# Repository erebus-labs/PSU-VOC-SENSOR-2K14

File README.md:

PSU VOC SENSOR PROJECT
==============

The PSU VOC SENSOR PROJECT is a multi-board and software approach to sensor data collection, specifically targetting K20 classrooms - All on an open source HW/SW stack.

The mutli-board solution allows for the independant and decoupled developement of custom sensors, while the open software stack allows custom interpolation of sensor readings. 

- [ ] Note that Some USB Drivers/custom communication drivers still need to be reworked before the entire project can be released under some flavor of Open Source Licensing (e.g. GPL v3?)

All of the Hardware and Software developed is available, keeping in mind that future revisions and use must maintain open source licensing.

#Schematics

##Main Board

##Sensor Boards

#Code

##uC 

##GUI

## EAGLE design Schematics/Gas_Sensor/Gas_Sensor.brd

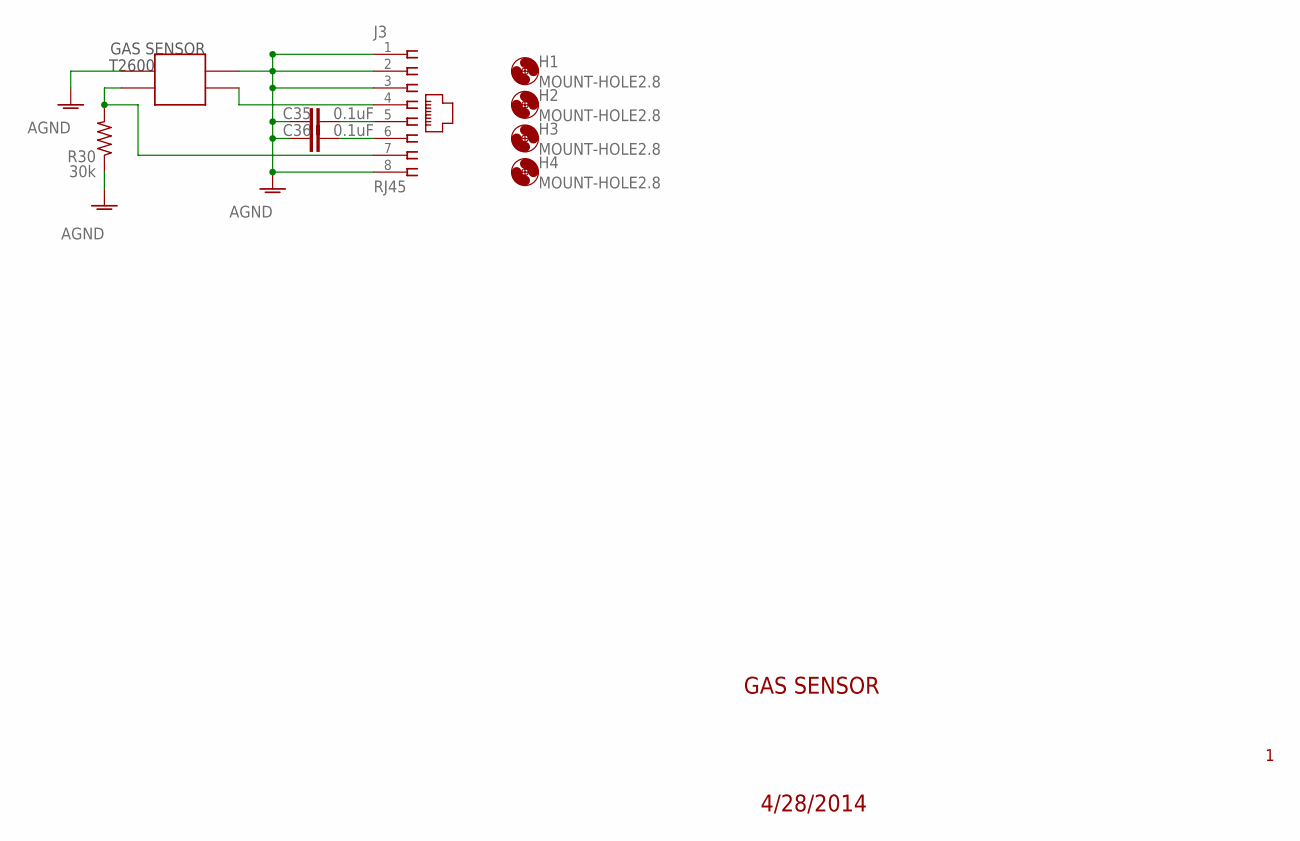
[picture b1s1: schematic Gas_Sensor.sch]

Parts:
C35, C36: 0.1uF; C0603K
H1, H2, H3, H4: MOUNT-HOLE2.8; 2,8
J3: RJ45; 555167-1
R30: 30k; R1206
X1: GAS_SENSOR

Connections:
AGND: C35.2, C36.2, J3.1, J3.2, J3.3, J3.8, R30.1, X1.P$1, X1.P$2
unnamed: J3.4, X1.P$3
unnamed: J3.7, R30.2, X1.P$4
unnamed: C36.1, J3.6
unnamed: C35.1, J3.5

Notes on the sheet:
GAS SENSOR
T2600
4/28/2014

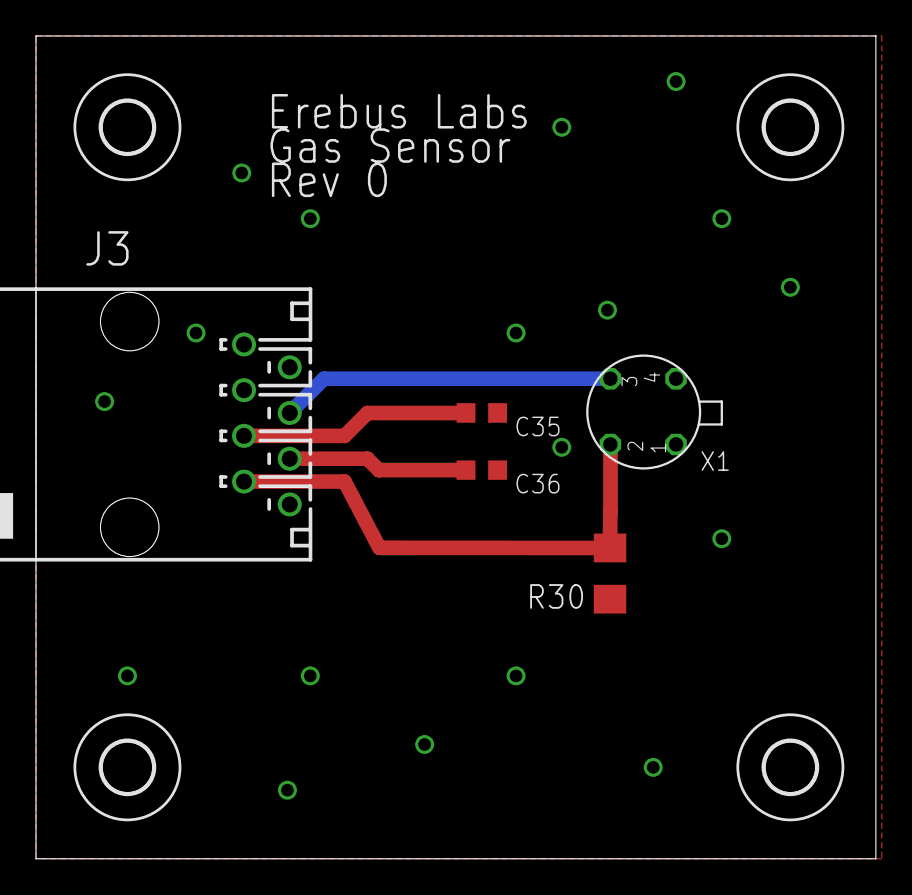
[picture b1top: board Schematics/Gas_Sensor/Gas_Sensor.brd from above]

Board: 2 copper layers, 46.7 x 45.7 mm, 9 parts (0 on the bottom side), 5 nets.

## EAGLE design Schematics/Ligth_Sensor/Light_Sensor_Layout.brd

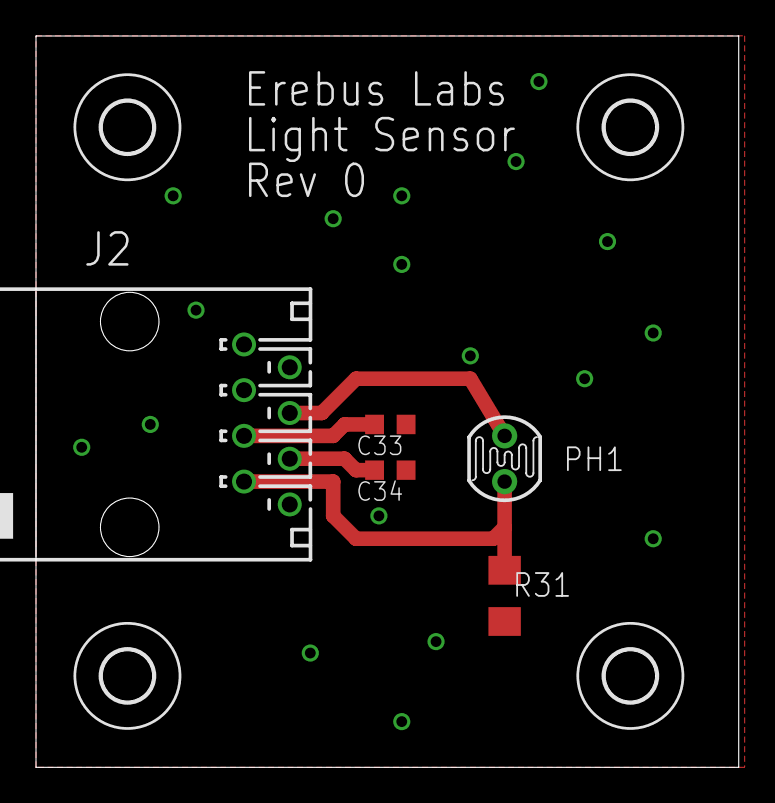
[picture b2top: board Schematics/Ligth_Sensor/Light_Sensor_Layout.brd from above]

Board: 2 copper layers, 39.0 x 40.6 mm, 9 parts (0 on the bottom side), 5 nets.

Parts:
C33, C34: 0.1uF; C0603K
H1, H2, H3, H4: MOUNT-HOLE2.8; 2,8
J2: RJ45; 555167-1
PH1: VT90N2; VT900
R31: 10k; R1206

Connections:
AGND: C33.1, C34.1, J2.1, J2.2, J2.3, J2.8, R31.1
unnamed: J2.4, PH1.1
unnamed: J2.7, PH1.2, R31.2
unnamed: C33.2, J2.5
unnamed: C34.2, J2.6

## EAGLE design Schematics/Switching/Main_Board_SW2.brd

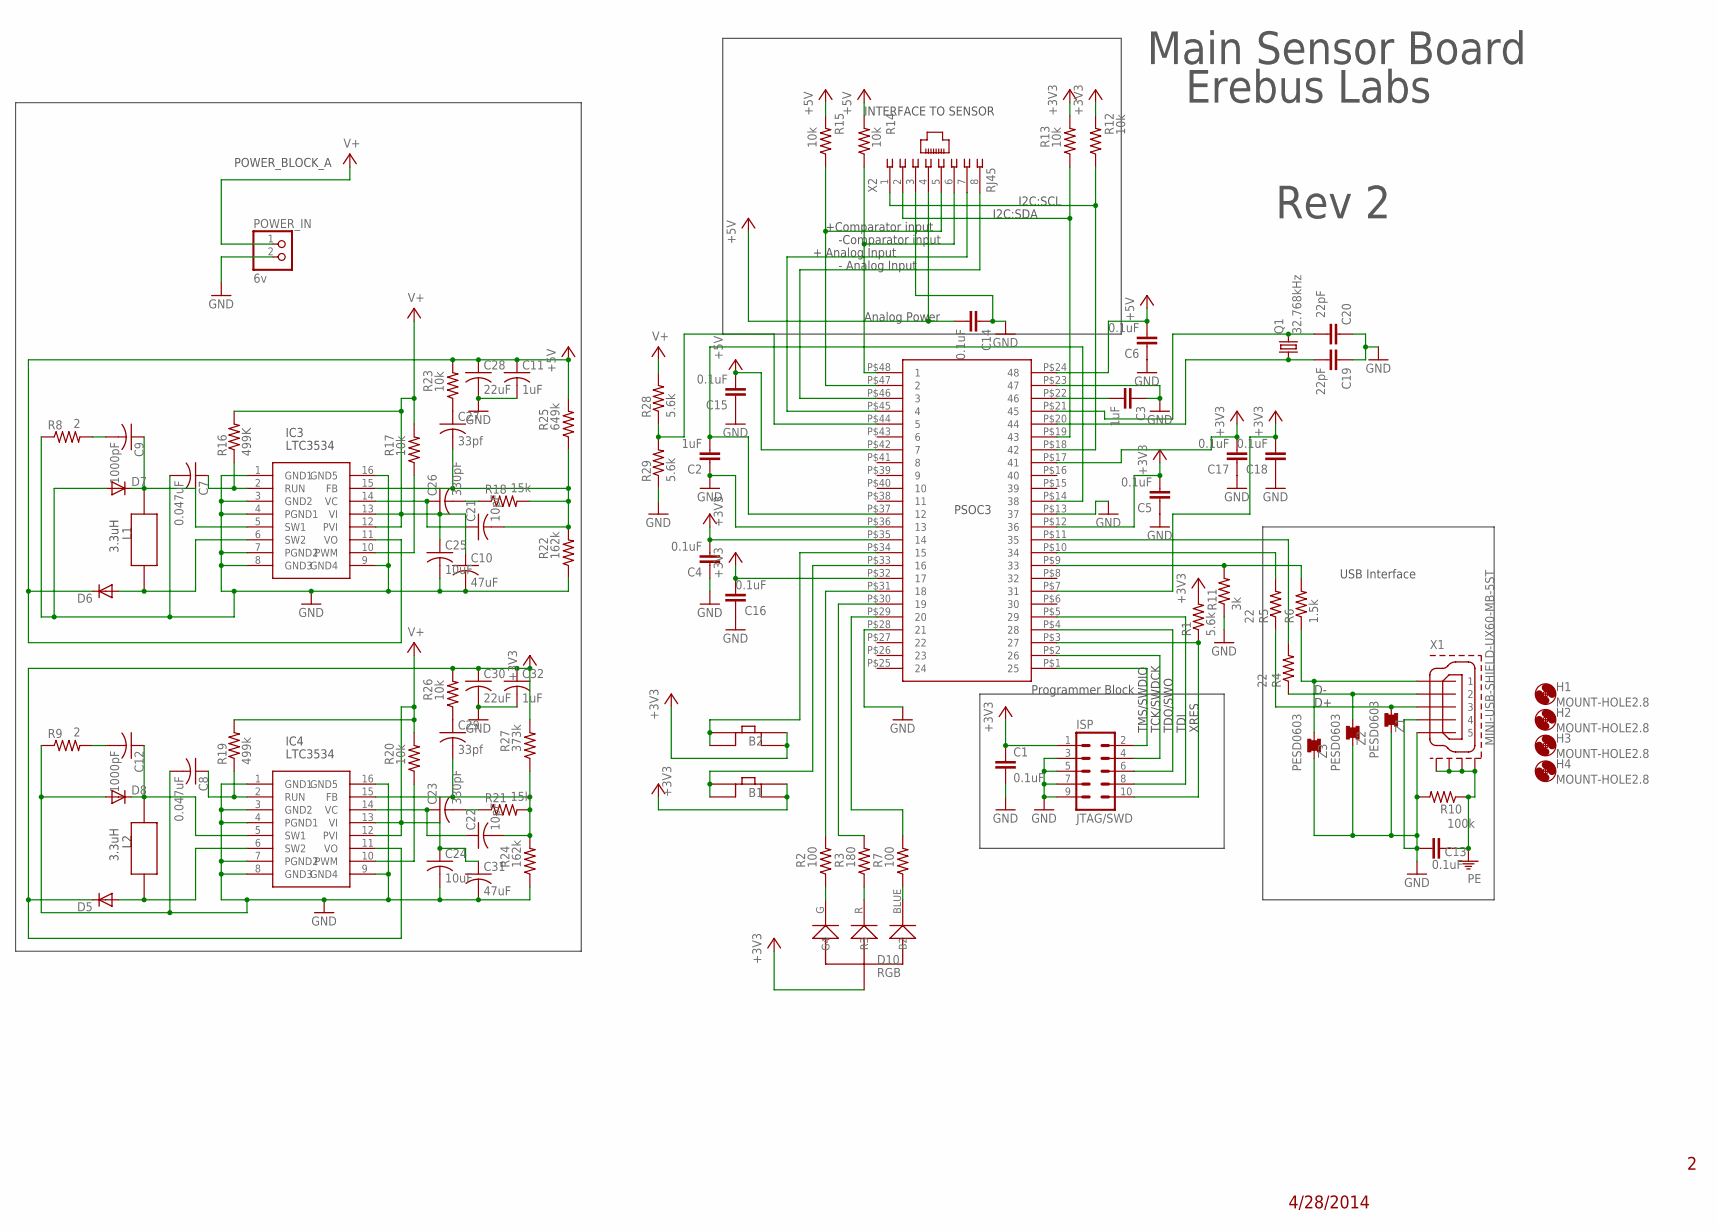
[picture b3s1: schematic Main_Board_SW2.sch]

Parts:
C1, C4, C5, C6, C13, C14, C15, C16, C17, C18: 0.1uF; C0603K
C2, C3, C11, C32: 1uF; C0603
C7, C8: 0.047uF; C0402
C9, C12: 1000pF; C0402
C10, C31: 47uF; C1210
C19, C20: 22pF; C0603
C21, C22: 10pF; C0805
C23, C26: 330pF; C0805
C24, C25: 10uF; C0805
C27, C29: 33pf; C0805
C28, C30: 22uF; C0805
D5, D6, D7, D8: DIODE-SOD323-R; SOD323-R
H1, H2, H3, H4: MOUNT-HOLE2.8; 2,8
IC3, IC4: SWITCHER; SSOP16
ISP: JTAG/SWD; FTSH-105-01-L-DV-K
L1: 3.3uH; SHEILDED_COIL
L2: 4.7uH; SHEILDED_COIL
POWER_IN: 6v; 1X02
Q1: 32.768kHz; TC38H
R1, R28, R29: 5.6k; R0805
R2, R7: 100; R0805
R3: 180; R0805
R4, R5: 22; R0603
R6: 1.5k; R0805
R8, R9: 2; R0402
R10: 100k; R0805
R11: 3k; R0805
R12, R13, R14, R15, R17, R20, R23, R26: 10k; R0805
R16: 499K; R0805
R18, R21: 15k; R0805
R19: 499k; R0805
R22, R24: 162k; R0805
R25: 649k; R0805
R27: 373k; R0805
RGB_LED: RGB_LED
U$1: PSOC_3_48PIN_SSOP
U$5, U$6: SPST
X1: MINI-USB-SHIELD-UX60-MB-5ST; UX60-MB-5ST
X2: RJ45; 555167-1
Z1, Z2, Z3: PESD0603; SMD-0603

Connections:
+3V3: C1.1, C4.2, C5.2, C16.2, C17.2, C18.2, C30.1, C32.1, D5.C, IC4.11 (VO), ISP.1, R1.2, R12.2, R13.2, R26.2, R27.2, RGB_LED.VCC (VCC1), U$1.P$7 (31), U$1.P$12 (36), U$1.P$17 (41), U$1.P$32 (17), U$1.P$35 (14), U$5.B1, U$5.B2, U$6.B1, U$6.B2
+5V: C6.2, C11.1, C14.2, C15.2, C28.1, D6.C, IC3.11 (VO), R14.2, R15.2, R23.2, R25.2, U$1.P$24 (48), U$1.P$42 (7), X2.4
ANALOGINPUT: U$1.P$46 (3), X2.8
GND: C1.2, C2.1, C3.1, C4.1, C5.1, C6.1, C7.2, C8.2, C10.2, C11.2, C13.2, C14.1, C15.1, C16.1, C17.1, C18.1, C19.1, C20.1, C24.2, C25.2, C28.2, C30.2, C31.2, C32.2, D7.A, D8.A, IC3.1 (GND1), IC3.3 (GND2), IC3.4 (PGND1), IC3.7 (PGND2), IC3.8 (GND3), IC3.9 (GND4), IC3.16 (GND5), IC4.1 (GND1), IC4.3 (GND2), IC4.4 (PGND1), IC4.7 (PGND2), IC4.8 (GND3), IC4.9 (GND4), IC4.16 (GND5), ISP.3, ISP.5, ISP.7, ISP.9, POWER_IN.2, R8.1, R9.1, R10.2, R11.1, R22.1, R24.1, R29.1, U$1.P$13 (37), U$1.P$23 (47), U$1.P$28 (21), U$1.P$36 (13), X1.4, X1.5, X2.3, Z1.1, Z2.1, Z3.1
unnamed: R4.2, U$1.P$11 (35)
unnamed: R5.2, U$1.P$10 (34)
unnamed: R6.2, R11.2, U$1.P$9 (33)
unnamed: ISP.2, U$1.P$1 (25)
unnamed: ISP.4, U$1.P$2 (26)
unnamed: ISP.6, U$1.P$4 (28)
unnamed: ISP.8, U$1.P$5 (29)
unnamed: ISP.10, R1.1, U$1.P$3 (27)
unnamed: C2.2, U$1.P$14 (38), U$1.P$37 (12)
unnamed: R2.1, RGB_LED.G (G4)
unnamed: C3.2, U$1.P$22 (46)
unnamed: R3.1, RGB_LED.R (R3)
unnamed: R5.1, X1.3, Z1.2
unnamed: R4.1, X1.2, Z2.2
unnamed: R7.1, RGB_LED.BLUE (B2)
unnamed: C20.2, Q1.2, U$1.P$21 (45)
unnamed: R6.1, X1.1, Z3.2
unnamed: R15.1, U$1.P$47 (2), X2.5
unnamed: R14.1, U$1.P$48 (1), X2.6
unnamed: R12.1, U$1.P$18 (42), X2.1
unnamed: R28.1, R29.2, U$1.P$44 (5)
unnamed: C19.2, Q1.1, U$1.P$20 (44)
unnamed: C21.1, C26.1, IC3.14 (VC)
unnamed: C7.1, IC3.2 (RUN), R16.1
unnamed: C9.1, D7.C, IC3.5 (SW1), L1.P$2
unnamed: IC3.10 (PWM), R17.1
unnamed: D6.A, IC3.6 (SW2), L1.P$1
unnamed: C26.2, R18.1
unnamed: C21.2, C27.2, IC3.15 (FB), R18.2, R22.2, R25.1
unnamed: C27.1, R23.1
unnamed: C8.1, IC4.2 (RUN), R19.1
unnamed: IC4.10 (PWM), R20.1
unnamed: C12.1, D8.C, IC4.5 (SW1), L2.P$2
unnamed: D5.A, IC4.6 (SW2), L2.P$1
unnamed: C22.1, C23.1, IC4.14 (VC)
unnamed: C23.2, R21.1
unnamed: C22.2, C29.2, IC4.15 (FB), R21.2, R24.2, R27.1
unnamed: C29.1, R26.1
unnamed: U$1.P$34 (15), U$5.A1, U$5.A2
unnamed: U$1.P$45 (4), X2.7
unnamed: R2.2, U$1.P$31 (18)
unnamed: U$1.P$33 (16), U$6.A1, U$6.A2
unnamed: R3.2, U$1.P$30 (19)
unnamed: R7.2, U$1.P$29 (20)
unnamed: R13.1, U$1.P$19 (43), X2.2
unnamed: C9.2, R8.2
unnamed: C12.2, R9.2
PE: C13.1, R10.1, X1.M1 (GND1), X1.M2 (GND2), X1.M3 (GND3), X1.M4 (GND4)
V+: C10.1, C24.1, C25.1, C31.1, IC3.12 (PVI), IC3.13 (VI), IC4.12 (PVI), IC4.13 (VI), POWER_IN.1, R16.2, R17.2, R19.2, R20.2, R28.2

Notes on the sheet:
PSOC3
TMS/SWDIO
TCK/SWDCK
TDO/SWO
TDI
XRES
Programmer Block
INTERFACE TO SENSOR
USB Interface
+Comparator input
-Comparator input
- Analog Input
I2C:SCL
I2C:SDA
3.3uH
POWER_BLOCK_A
Erebus Labs
Main Sensor Board
Rev 2
IC3
IC4
LTC3534
Analog Power
+ Analog Input
4/28/2014
D10
RGB

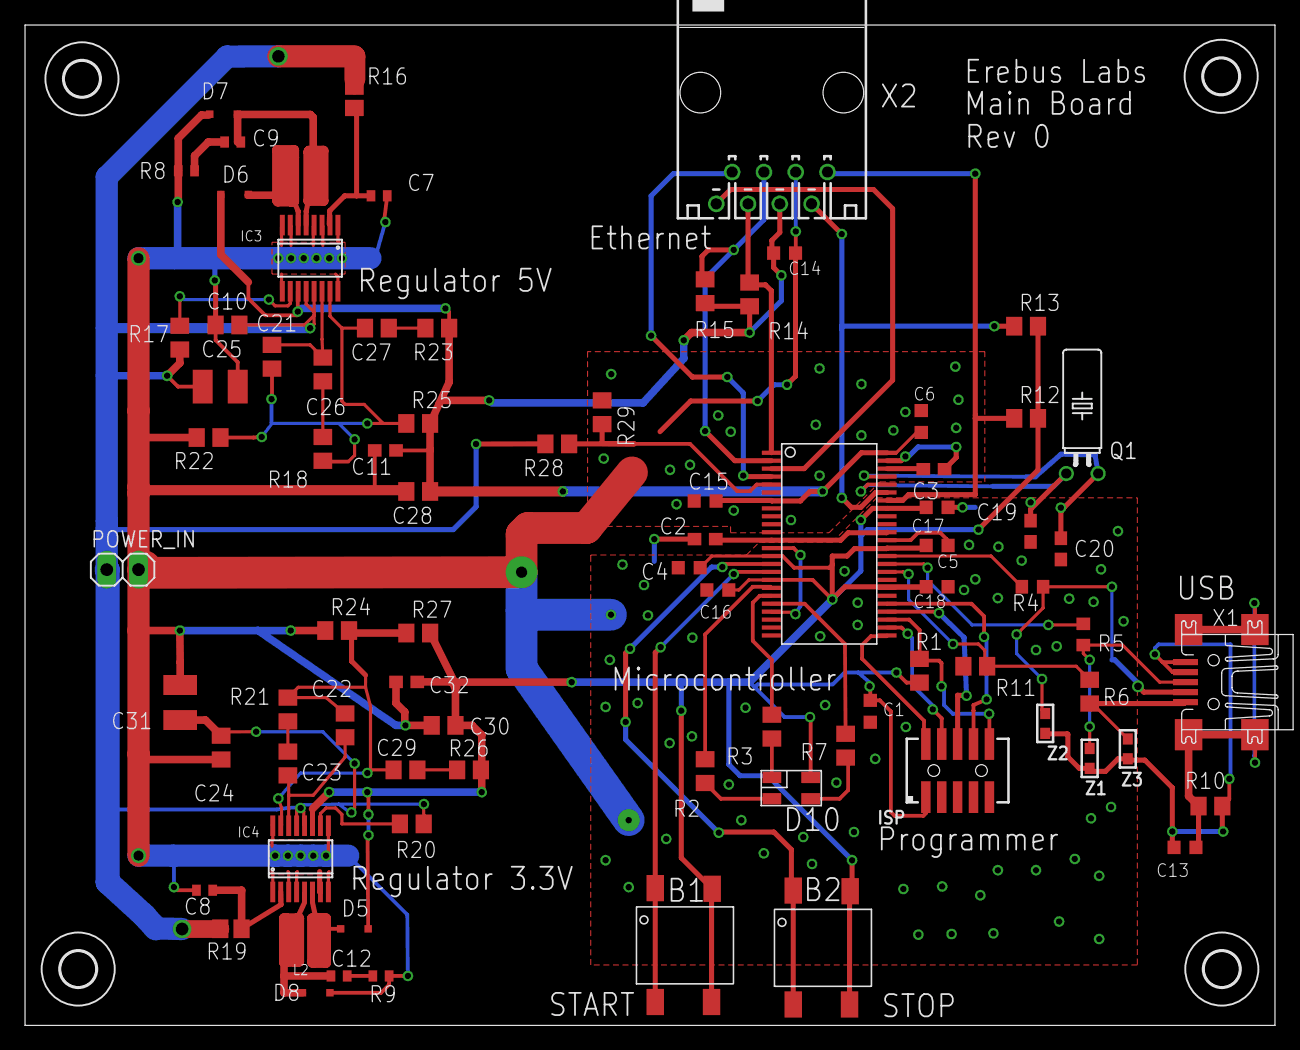
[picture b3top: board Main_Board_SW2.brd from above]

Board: 2 copper layers, 99.9 x 80.0 mm, 85 parts (0 on the bottom side), 53 nets.

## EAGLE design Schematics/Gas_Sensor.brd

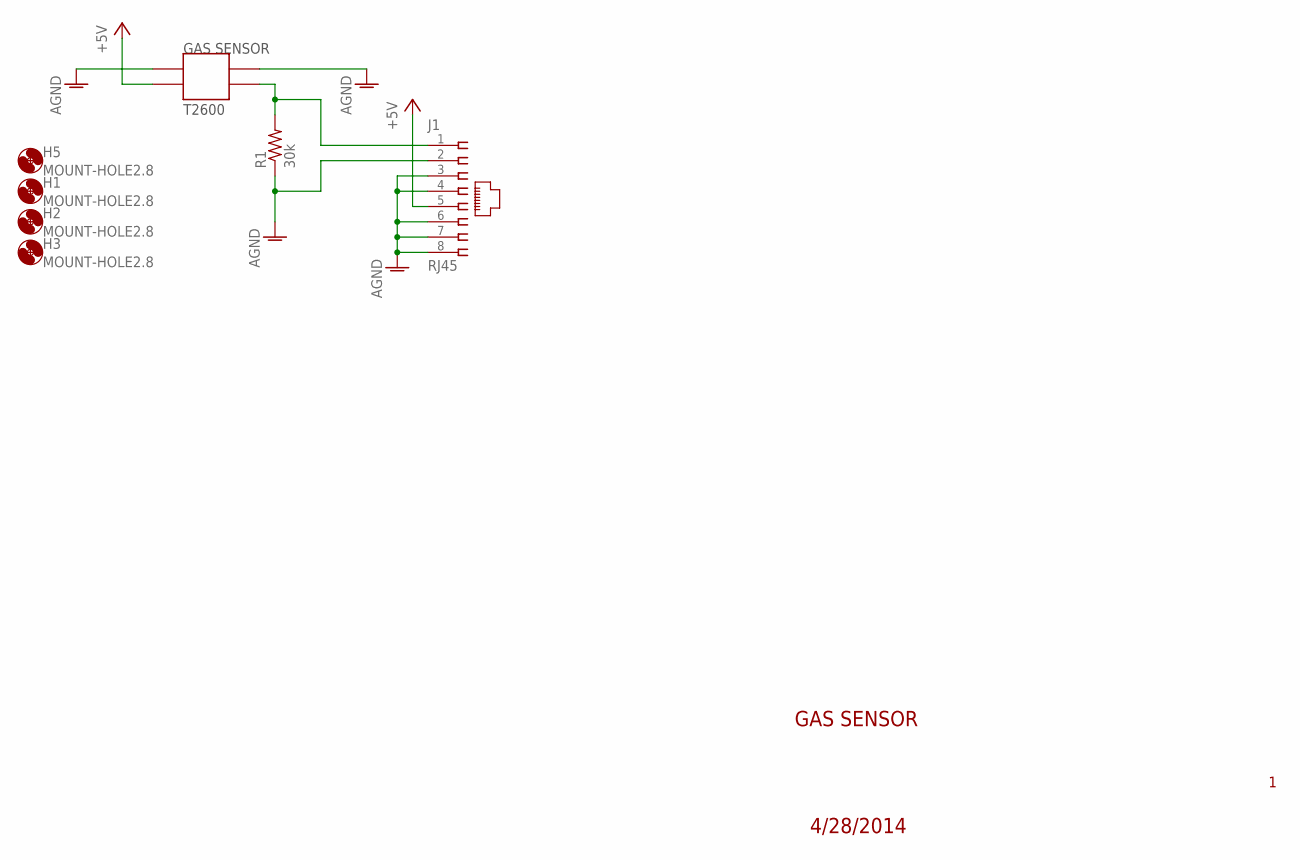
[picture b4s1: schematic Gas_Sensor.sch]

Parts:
H1, H2, H3, H5: MOUNT-HOLE2.8; 2,8
J1: RJ45; 555167-1
R1: 30k; R1206
U$1: GAS_SENSOR

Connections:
+5V: J1.5, U$1.P$3
AGND: J1.2, J1.3, J1.4, J1.6, J1.7, J1.8, R1.1, U$1.P$1, U$1.P$2
unnamed: J1.1, R1.2, U$1.P$4

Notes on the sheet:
GAS SENSOR
T2600
4/28/2014

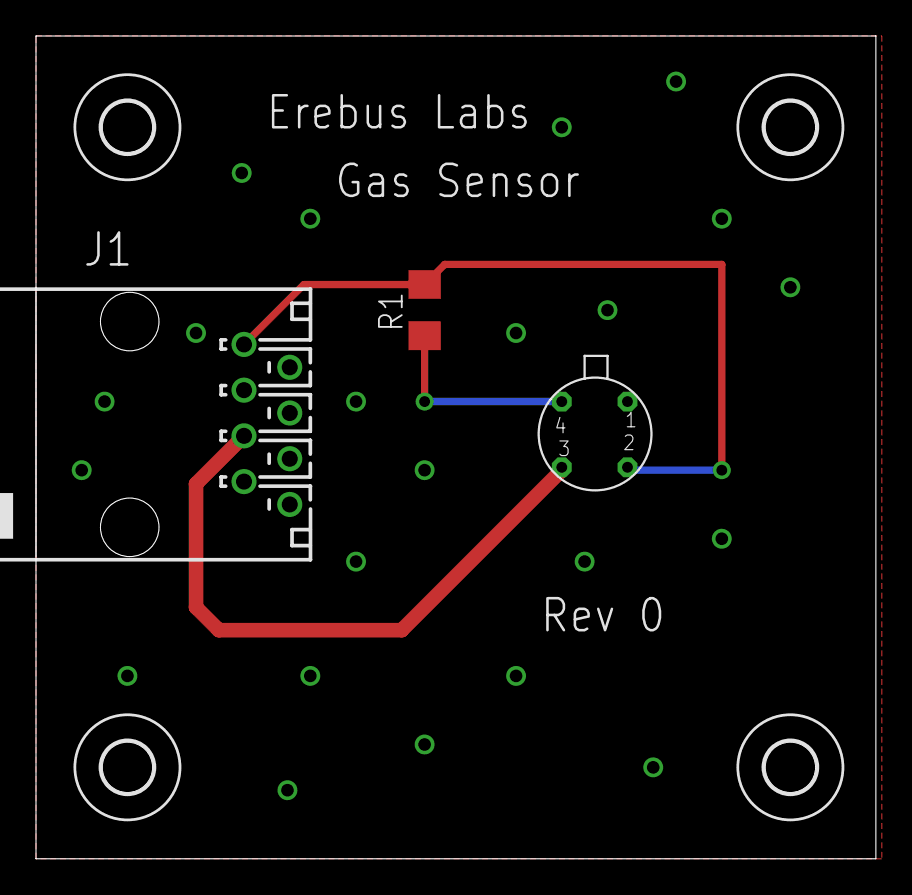
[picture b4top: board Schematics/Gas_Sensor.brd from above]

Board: 2 copper layers, 46.7 x 45.7 mm, 7 parts (0 on the bottom side), 3 nets.

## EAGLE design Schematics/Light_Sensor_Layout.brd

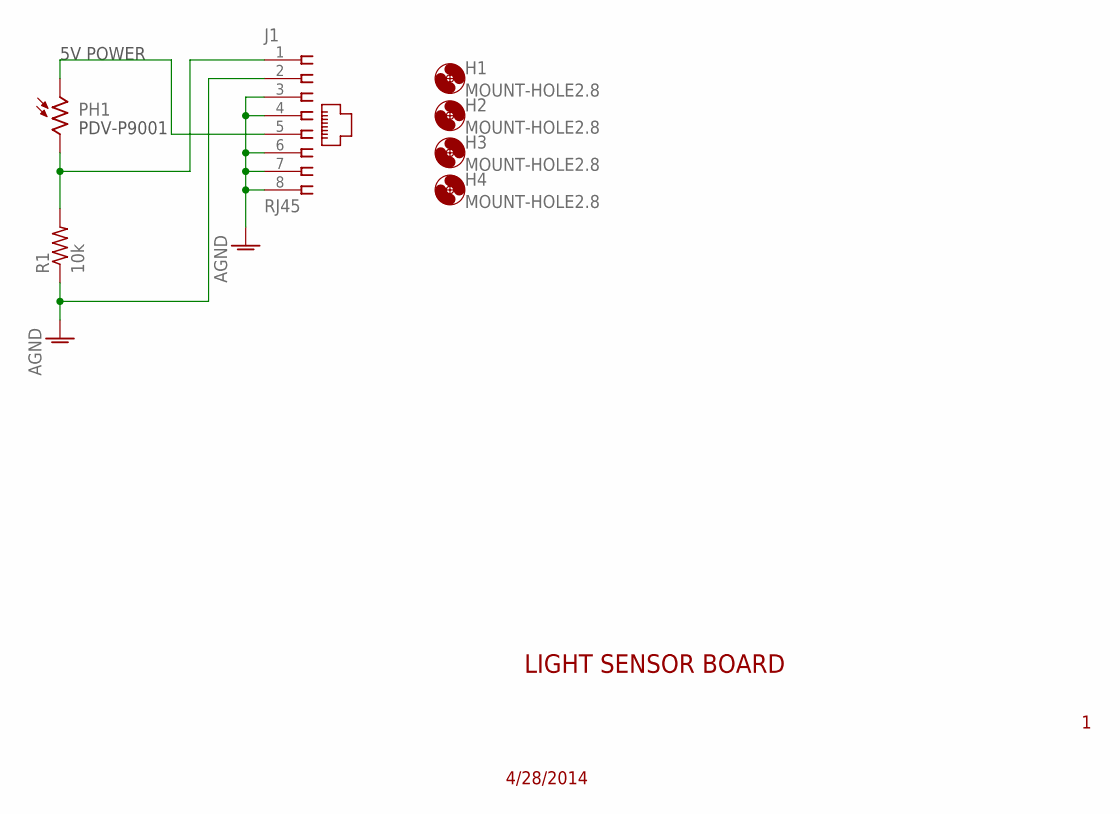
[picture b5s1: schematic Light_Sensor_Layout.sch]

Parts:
H1, H2, H3, H4: MOUNT-HOLE2.8; 2,8
J1: RJ45; 555167-1
PH1: VT83N2; VT800
R1: 10k; R1206

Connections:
AGND: J1.2, J1.3, J1.4, J1.6, J1.7, J1.8, R1.1
unnamed: J1.5, PH1.1
unnamed: J1.1, PH1.2, R1.2

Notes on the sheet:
PDV-P9001
5V POWER
LIGHT SENSOR BOARD
4/28/2014

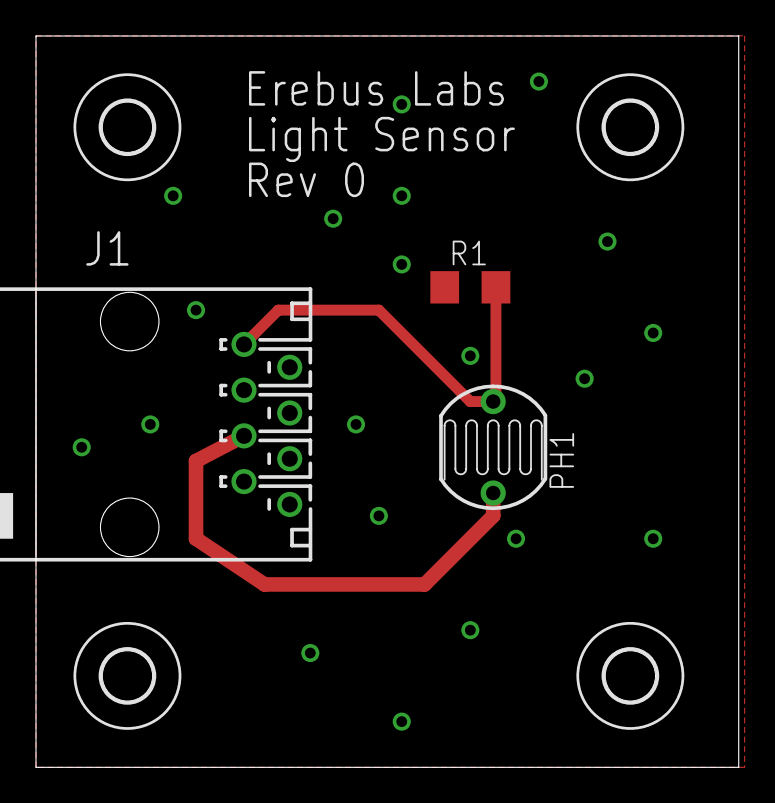
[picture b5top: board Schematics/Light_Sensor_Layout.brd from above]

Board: 2 copper layers, 39.0 x 40.6 mm, 7 parts (0 on the bottom side), 3 nets.

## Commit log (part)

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2013-12-27 Push test
2013-12-28 Test to see if I can update.
2013-12-28 Possible Parts
    Some parts that might work. The micrcontoller is probably to expensive.
2013-12-31 Added V1.0 of requirements doc
2013-12-31 Created /Documents folder, added initial requirements doc
2014-01-03 Needs Statments
    There are some format errors that show up whan saving an open offfice
    file as a .doc file
2014-01-03 Delete .~lock.Erebus_Needs.doc#
    Not sure why this file was created
2014-01-04 Initial Build
2014-01-04 Added objective and background document.
2014-01-04 Updated Requirements doc
2014-01-07 Removed Documents/Erebus_Needs.docx
2014-01-07 Delete .~lock.test 1.txt#
    Not sure why I made this, so it was removed
2014-01-08 Revert "Delete .~lock.test 1.txt#"
    This reverts commit 3fadf2508f8f2172cbb31cd926eae070e93d5b1f.
2014-01-08 Test 2
2014-01-08 Added references
2014-01-12 Added Documents/Budget.docx
2014-01-12 Removed testfile.c
2014-01-13 Initial Build. Needs Content
    Just an initial build. I need to fix some formatting and add some
    content, but I just wanted to put this up to show everyone the general
    theme so we have time to change things before the meeting.
2014-01-13 Fixed Name.
2014-01-13 Formatted Tables
2014-01-13 Added Content. Diagrams and Milestones
2014-01-13 Original File for System Diagram.
2014-01-13 Original File for Interfacing Diagram.
2014-01-14 Renamed. Should not be labeled as a build.
2014-01-14 Updated Proposal
2014-01-15 Create gh-pages branch via GitHub
2014-01-18 Temp sensor
2014-01-19 Removed old proposal PDF
2014-01-19 Updated proposal to v1.3
2014-01-19 Removed Erebus_Needs.doc from main directory
2014-01-19 Removed PSoC 4100 Family datasheet
2014-01-20 Added microcontroller specifications for top 3 candidates
2014-01-22 Updated uController specs
2014-01-22 Quick Meeting Notes
2014-01-23 Updated Microcontroller_Specs.xlsx with PCB costs
2014-01-23 Added initial software plan
2014-01-24 Added preliminary block diagram file. File contains multiple pages with different levels.
    Requires MS Visio
2014-01-25 Updated with lower level diagrams (1 and 2) as well as block diagram from datasheet for ucontroller.
2014-01-25 No longer needed
2014-01-27 Cleaned up microcontroller datasheets
2014-01-30 Timeline. Added Hardware/Firmware Subtasks. ~80% Complete
2014-01-31 Replaced TI datasheets with Cypress datasheets for PSoC3
2014-01-31 Removed obsolete documents
2014-01-31 Possible emperature sensor
2014-01-31 Temperature sensor
    Cheaper version of previous one.
2014-01-31 Not using
2014-01-31 Updated Budget to v1.3
2014-02-01 Updated Design Spec and Budget
2014-02-02 Added contacts document
2014-02-02 Added contact list document
2014-02-16 Added Highlights to ADC Section
2014-02-16 Added Cypress ADC Example
2014-02-16 Added ADC Datasheet with Highlights
2014-02-16 Added Figaro Sensor Datasheets with Highlights.
2014-02-23 Early version of main board schematic
2014-03-01 Added Highlights to Emulated EEPROM
2014-03-04 Updated Design Specification with USB details
2014-03-14 Initial Push of Max Code Folder
2014-03-14 Added dev board user guide
2014-03-15 Added EEPROM datasheet
2014-03-21 Mac Code Update
2014-03-24 Updated Scott Project files, added datasheets, initial push of Python Script
2014-03-27 Added USB communication protocol and EEPROM access functions
2014-03-27 Repush Repush
2014-03-27 Created Demo Build. Merged Code
2014-03-27 Updated communication script
2014-03-27 Updated Demo Code
2014-03-28 Push Code
2014-03-28 Added Interrupt Documentation
2014-03-28 Completed USB data dump method
2014-03-28 Fixed Data dump methods
2014-03-29 Updated Schematic
    Grounds and voltages are not set yet. Most are place holders for the
    moment.
2014-03-30 Updated Design Spec to v1.4
2014-03-30 Fixed typos in Design Spec
2014-04-01 Updated Design Spec to v1.5
2014-04-01 Added files for Bryan
    Added code to folder for testing power management and RTC interrupt
    controls.
2014-04-02 Initial push of gui.py
2014-04-02 Implemented EEPROM variable pointers
2014-04-02 Changed incoming stream parsing to count bytes instead of data samples
2014-04-02 Spread Sheet did not port to pdf properly
2014-04-09 Update push
2014-04-10 Added hard_reset() and EEPROM variables, removed blinking LED
2014-04-10 Updated master to match Scott code from commit 5fe109704ac546addd07589f49c463d76ea794e6
2014-04-10 Cleaned up python directory, created simple interface
2014-04-10 Updated PM code, added reference doc
    Added RTC interrupt mask functions
    Added RTC sample unit check
    Added Sample code
    Added C reference document
2014-04-13 Updated GUI Layout: Added buttons, frames, and menu
2014-04-14 Restructured GUI file layout. Began integrating sensor class with GUI - sensor now connects.
2014-04-15 Add switcher circuit
2014-04-15 BOM and schematic update
    Still missing push button interface and sensor breakouts
2014-04-20 File Cleaning
2014-04-23 Misc changes to power mgmt code
2014-04-25 Stuff
2014-04-26 Massive changes to master. Rearranged layout, added multiple sample block data support, added button interrupts, added send configuration routine, added data sample block headers
2014-04-26 Small fix on pin1 of psoc
2014-04-26 Changed command format to single byte
2014-04-28 Fixed applying and retrieving settings changes
2014-04-28 Created BreadBoardBuild in Master folder. Began Pin assign
    USB is Set. VDDD VDDA VDDIO Set. Questions on JTAG
2014-04-28 Fixed multiple sample block transfer and button interrupts
2014-04-28 Fixed multiple sample block transfers
2014-04-29 Mostly updates with some sensor stuff
2014-04-30 Fixed timestamps on data samples
2014-04-30 Added recognition of empty data sets
2014-05-01 Updates for pin assignments
2014-05-02 Fixed sample function not being called Changed sleep function call values to match Cypress defined variables Changed sleep time to "none"
    Sample counter not correctly detecting when sample should occur based on given interval
2014-05-02 Removed LED test code from everywhere but the sample function
2014-05-02 Button Updates
2014-05-02 Sleep functionality working Sample functionality working
    Removed unneeded interval unit masks
    standardized function names
2014-05-02 Deleted Initial BreadBoardBuild.
2014-05-02 Fixed interface.py handling of multi-packet data transfers, cleaned up unnecessary files
2014-05-02 Fixed multi-packet data dumps with extra interlocking and zero-length packets
2014-05-06 Cleaned up some power code
    Added initial poster template with base design
2014-05-07 Broken code checkpoint. LED controls added, debouncers removed, sleep code ifdef'd off
2014-05-08 Switching Layout Placed
2014-05-08 Fixed sample start/stop with sleep. Added RGB LED Control. Reorganized code tree and added macro and global header files.
2014-05-08 Layout Update
2014-05-08 Began PCB Verify. Slight Modifications to Gas Sensor Module during verify.
2014-05-09 LDO Layout
2014-05-10 Added Drill Holes. Moved Traces. Moved Silkscreen References
2014-05-11 Added low power LED blinking. Added more 3rd party docs.
2014-05-11 Layout for final inspection
2014-05-12 Added Poster
2014-05-12 Added grading rubric files
2014-05-12 Manufacturer part number updates
2014-05-12 PCB Verify Push. Status: In Progress
2014-05-12 Updated Switcher Board
2014-05-13 PCB Verified. Add Battery Sense
2014-05-13 Batter Sense
2014-05-13 Hopeful pull
2014-05-13 Updated Board PNGs
2014-05-13 Last layout sync of night
2014-05-15 Dimensions for each of the boards
2014-05-17 Added board enclosure files
2014-05-19 Flash persistence/wear-levelling implemented - corner cases not yet tested
2014-05-19 Implemented reset code in GUI. Removed save/restore settings options.
2014-05-19 Updated logo
    Updated Poster.pptx
    + Added Overview
    + Added references
    =Updated schematic printouts
    =Updated team info
    Added board enclosures (box) files
2014-05-20 Restored zero-length packet on sample export. Data persistence implementation complete. Pointer wrapping and memory full condition untested.
2014-05-20 Merged host/device replies, switch order of command characters. Moved next command in data dump.
2014-05-20 Added sucess messages to reset and data export
2014-05-24 Added comments to all functions
2014-05-24 Added docstrings and additional comments to GUI scripts
2014-05-26 Updated Poster.pptx +Added additional graphics =Changed som formatting and layout of overview =Changed layout of team section
2014-05-26 Cleaned up stuff
    Made Schematics easier to read
    Split Supplies in BOM and made names match references
    Renamed parts on sensor
2014-05-26 Changed Poster.pptx +Added final result section =Formatting adjustments =Moved objective to yellow section -Removed second overview paragraph -Less words
2014-05-27 Updated Poster.pptx to preliminary final version *Missing GUI pic *Missing Team pics *Needs proof reading and confirmation from team-mates
    Added PDF version of poster
2014-05-27 Fixed indentation errors in GUI script
2014-05-27 Small grammatical changes
2014-05-27 Thank god for version control
    Wrote over the wrong one
2014-05-27 Added Notes .pdf for Poster
2014-05-27 Added poster back or whatever
2014-05-28 Final version of Poster.pptx including initial feedback
2014-05-28 Poster stuff
2014-05-28 Minor adjustments to final poster
2014-05-29 Pushed up old file that got over worte
2014-05-30 Created Dev Board Master and Master. Updated IO for PCB
2014-05-31 Added notification box on settings application completion
2014-05-31 Fixed misnamed reset function call
2014-05-31 Is this the code youre looking for?
2014-06-02 Removed Scott's code folder
2014-06-02 Removed Max's code folder
2014-06-02 Removed DemoBuild code folder
2014-06-02 Removed extraneous text file from code folder
2014-06-02 Renamed master to master_pcb
2014-06-02 Updated master_pcb with correct pin assignments
2014-06-02 Removed incomplete file submission (Master folder)
2014-06-02 Removed every second battery check used for debugging
2014-06-02 Refactored button masks and PICU register out of RTC interrupt file
2014-06-02 Updated master_devboard with fixes from master_pcb
2014-06-02 Updated Project timeline. Original project file corrupted and removed, pdfs provided
2014-06-02 Removed old timeline pdf
2014-06-02 Updated budget with PCB and Digikey order info
2014-06-02 Added Cypress USBUART Windows drivers
2014-06-03 Cost for single unit
2014-06-03 Added sensor and power section to design specs.
2014-06-03 Added to the budget
2014-06-04 Added presentation file
2014-06-04 User Manual
2014-06-05 Initial Push of Basic STEM Lesson
    In Scott's favorite format. (Sorry)
2014-06-05 v1.6 of Design Spec
2014-06-05 Reorganized Documents Directory
2014-06-05 Fixed layout of BOM
2014-06-05 Added Technical Reference Manual
2014-06-05 Added Technical Reference Manual source doc, removed extra TRM PDF
2014-06-05 Fundamentals Edit. Moved some 3rd_Party_Docs
2014-06-05 Updated presentation to Final Rough Draft
2014-06-05 Changed sensor #1 to Gas sensor, added sensor #2: Custom sensor
2014-06-05 Added support for opening reference documents
2014-06-05 Added reference documents for GUI use
2014-06-06 Pushed The Test Plan! Update Format.
2014-06-06 Updated presentation
2014-06-06 Updated notes for me.
2014-06-06 PPT Updates
2014-06-06 Added static keyword to necessary functions, reordered function definitions so prototypes could be removed, fixed loop in update_settings(), moved header inclusions to *.c files
2014-06-06 Updated PPT Notes
2014-06-06 Pictures add
2014-06-11 Added Flash wear-levelling diagram
2014-06-12 Updated report to final version
2014-06-18 Updated enclosure files added Old files moved to folder
2014-06-18 Fixed the holes... again...
2014-08-29 Updated to readme
    Barebones updates, and images

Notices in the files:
parts and their libraries:
supressor: Copyright (C) 2009, Bob Starr
